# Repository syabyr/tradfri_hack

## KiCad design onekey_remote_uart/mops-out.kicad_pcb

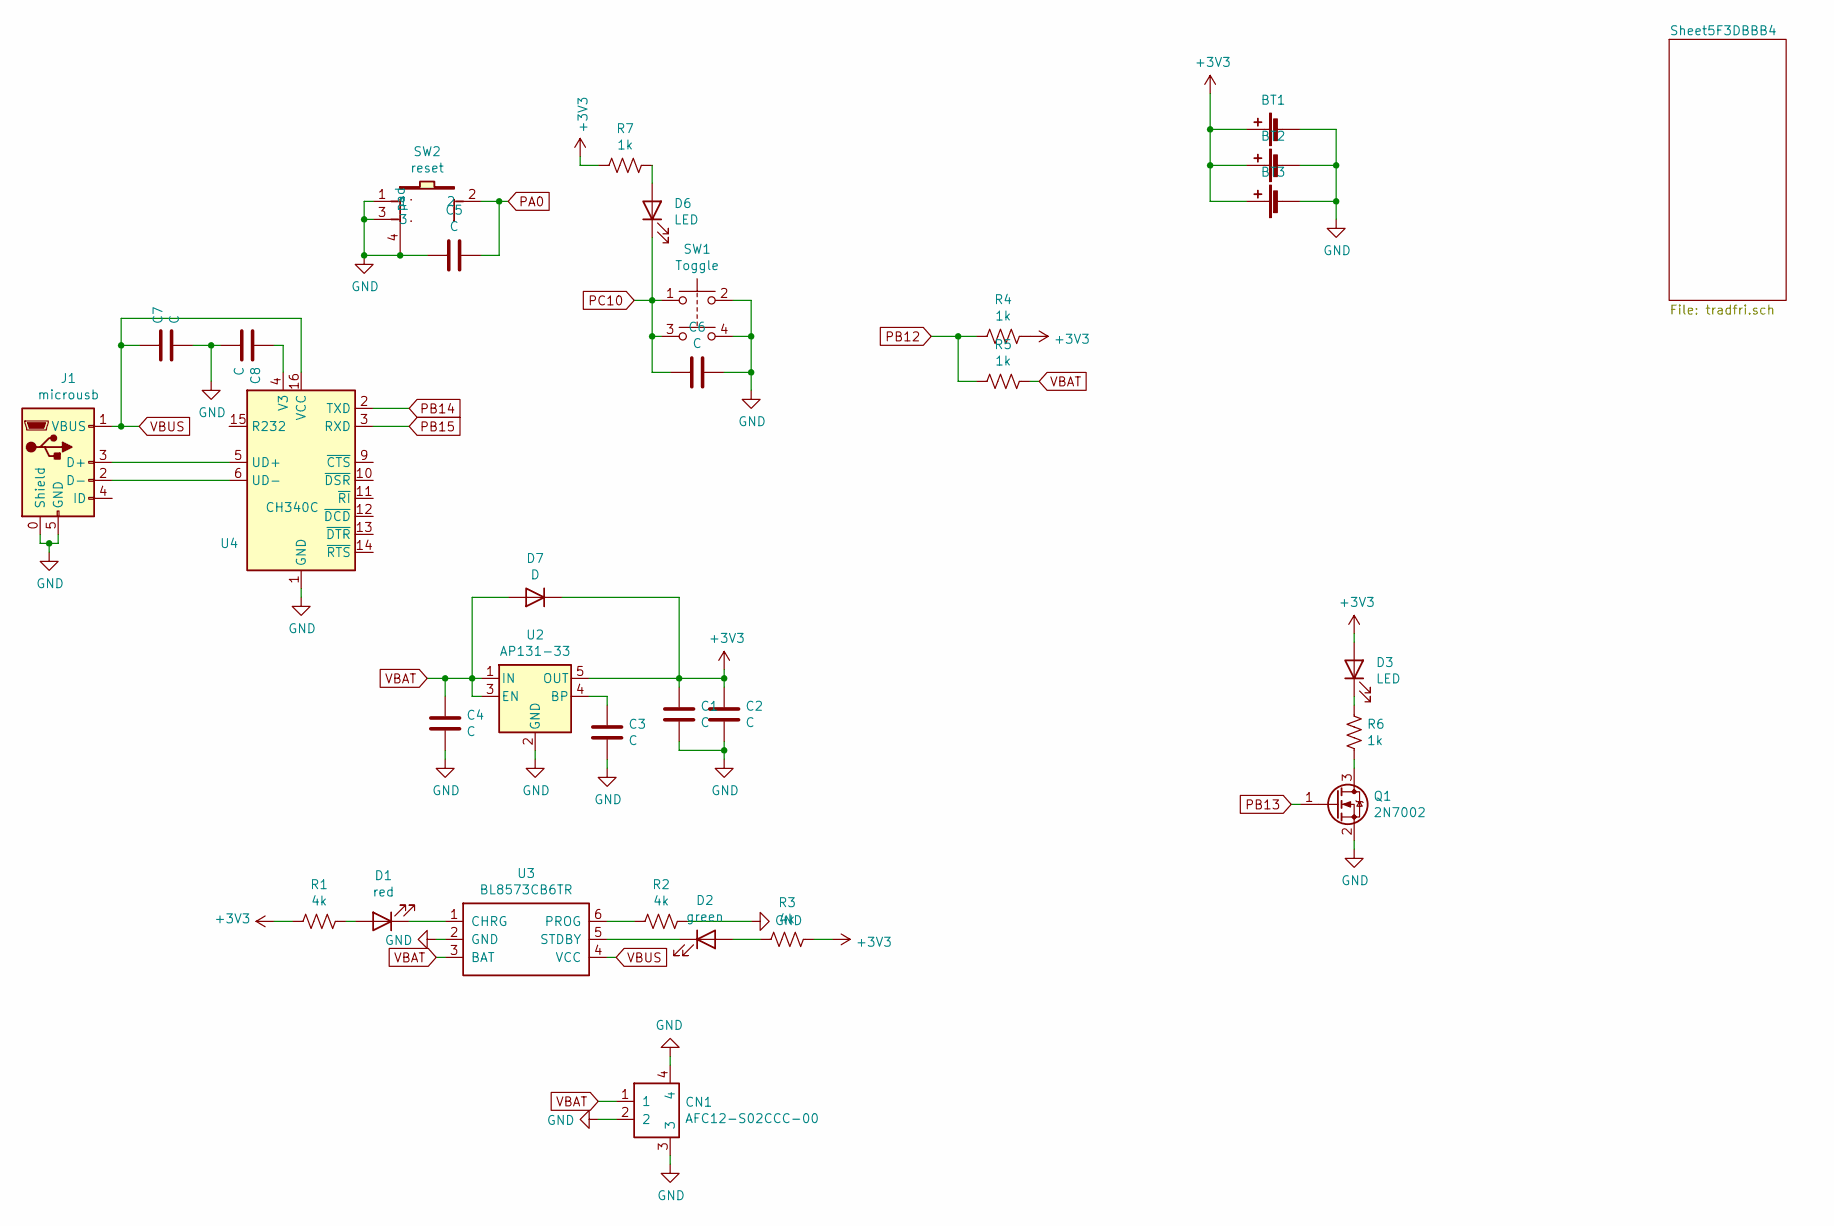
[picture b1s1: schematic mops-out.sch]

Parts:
BT1: Battery_Cell; CR2032_HOUSING
BT2: Battery_Cell; BAT-TH_BS-2-1
BT3: Battery_Cell; BAT-TH_CR2032-BS-6-1
C1, C3, C7, C8: C; C_0402_1005Metric_Pad0.74x0.62mm_HandSolder
C2, C4, C5, C6: C; C_0603_1608Metric_Pad1.08x0.95mm_HandSolder
CN1: AFC12-S02CCC-00; CONN-SMD_AFC12-S02CCC-00
D1: red; LED_0603_1608Metric_Pad1.05x0.95mm_HandSolder
D2: green; LED_0603_1608Metric_Pad1.05x0.95mm_HandSolder
D3, D6: LED; LED_0805_2012Metric_Pad1.15x1.40mm_HandSolder
D7: D; D_0603_1608Metric_Castellated
J1: microusb; USB_Micro-B_Wuerth_629105150521_CircularHoles
Q1: 2N7002; SOT-23
R1, R2, R3: 4k; R_0402_1005Metric_Pad0.72x0.64mm_HandSolder
R4, R5, R6, R7: 1k; R_0603_1608Metric_Pad0.98x0.95mm_HandSolder
SW1: Toggle; KEY-SMD_4P-L5.2-W5.2-P3.70-LS6.4-MOPS
SW2: reset; KEY_ALPS_SKRTLBE010
U2: AP131-33; SOT-23-5
U3: BL8573CB6TR; SOT-23-6_Handsoldering
U4: CH340C; SOIC-16_3.9x9.9mm_P1.27mm

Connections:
+3V3: BT1.1 (+), BT2.1 (+), BT3.1 (+), C1.1, C2.1, D3.2 (A), D7.1 (K), R1.2, R3.1, R4.1, R7.2, U2.5 (OUT); also elsewhere on the board
GND: BT1.2 (-), BT2.2 (-), BT3.2 (-), C1.2, C2.2, C3.2, C4.2, C5.2, C6.1, C7.2, C8.2, CN1.2, CN1.3, CN1.4, J1.0 (Shield), J1.5 (GND), Q1.2 (S), R2.1, SW1.2, SW1.4, SW2.1, SW2.3, SW2.4 (pad), U2.2 (GND), U3.2 (GND), U4.1 (GND); also elsewhere on the board
unnamed: C3.1, U2.4 (BP)
unnamed: C8.1, U4.4 (V3)
unnamed: D1.1 (K), U3.1 (CHRG)
unnamed: D1.2 (A), R1.1
unnamed: D2.1 (K), U3.5 (STDBY)
unnamed: D2.2 (A), R3.2
unnamed: D3.1 (K), R6.1
unnamed: D6.2 (A), R7.1
unnamed: J1.2 (D-), U4.6 (UD-)
unnamed: J1.3 (D+), U4.5 (UD+)
unnamed: Q1.3 (D), R6.2
unnamed: R2.2, U3.6 (PROG)
PA0: C5.1, SW2.2; also elsewhere on the board
PB12: R4.2, R5.2; also elsewhere on the board
PB13: Q1.1 (G); also elsewhere on the board
PB14: U4.2 (TXD); also elsewhere on the board
PB15: U4.3 (RXD); also elsewhere on the board
PC10: C6.2, D6.1 (K), SW1.1, SW1.3; also elsewhere on the board
VBAT: C4.1, CN1.1, D7.2 (A), R5.1, U2.1 (IN), U2.3 (EN), U3.3 (BAT)
VBUS: C7.1, J1.1 (VBUS), U3.4 (VCC), U4.16 (VCC)

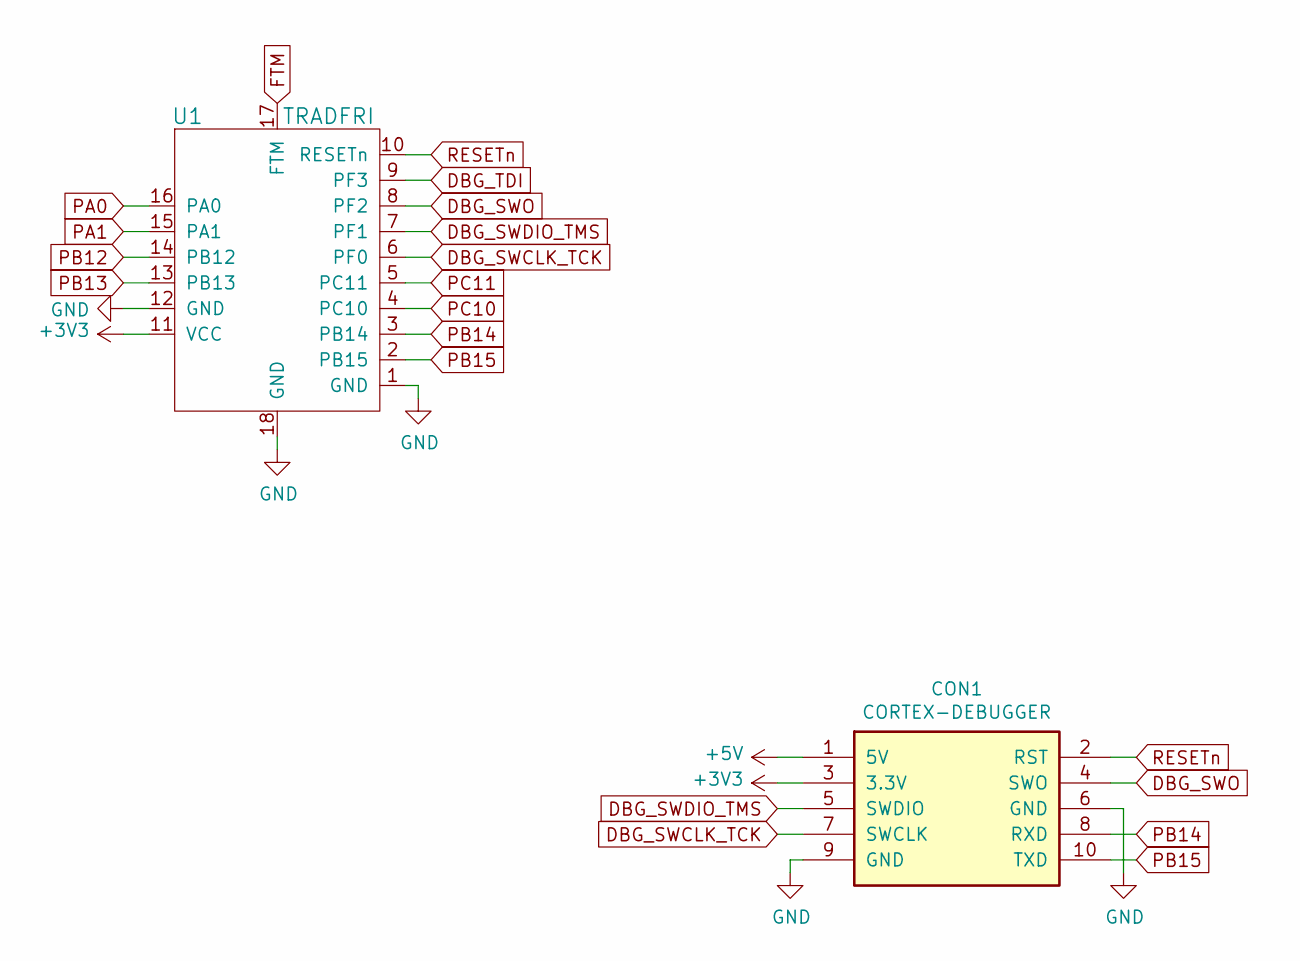
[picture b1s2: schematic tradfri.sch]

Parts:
CON1: CORTEX-DEBUGGER; debugger_2x05_P1.27mm_Vertical
U1: TRADFRI

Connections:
+3V3: CON1.3 (3.3V), U1.11 (VCC); also elsewhere on the board
+5V: CON1.1 (5V)
DBG_SWCLK_TCK: CON1.7 (SWCLK), U1.6 (PF0)
DBG_SWDIO_TMS: CON1.5 (SWDIO), U1.7 (PF1)
DBG_SWO: CON1.4 (SWO), U1.8 (PF2)
DBG_TDI: U1.9 (PF3)
FTM: U1.17 (FTM)
GND: CON1.6 (GND), CON1.9 (GND), U1.1 (GND), U1.12 (GND), U1.18 (GND); also elsewhere on the board
PA0: U1.16 (PA0); also elsewhere on the board
PA1: U1.15 (PA1)
PB12: U1.14 (PB12); also elsewhere on the board
PB13: U1.13 (PB13); also elsewhere on the board
PB14: CON1.8 (RXD), U1.3 (PB14); also elsewhere on the board
PB15: CON1.10 (TXD), U1.2 (PB15); also elsewhere on the board
PC10: U1.4 (PC10); also elsewhere on the board
PC11: U1.5 (PC11)
RESETn: CON1.2 (RST), U1.10 (RESETn)

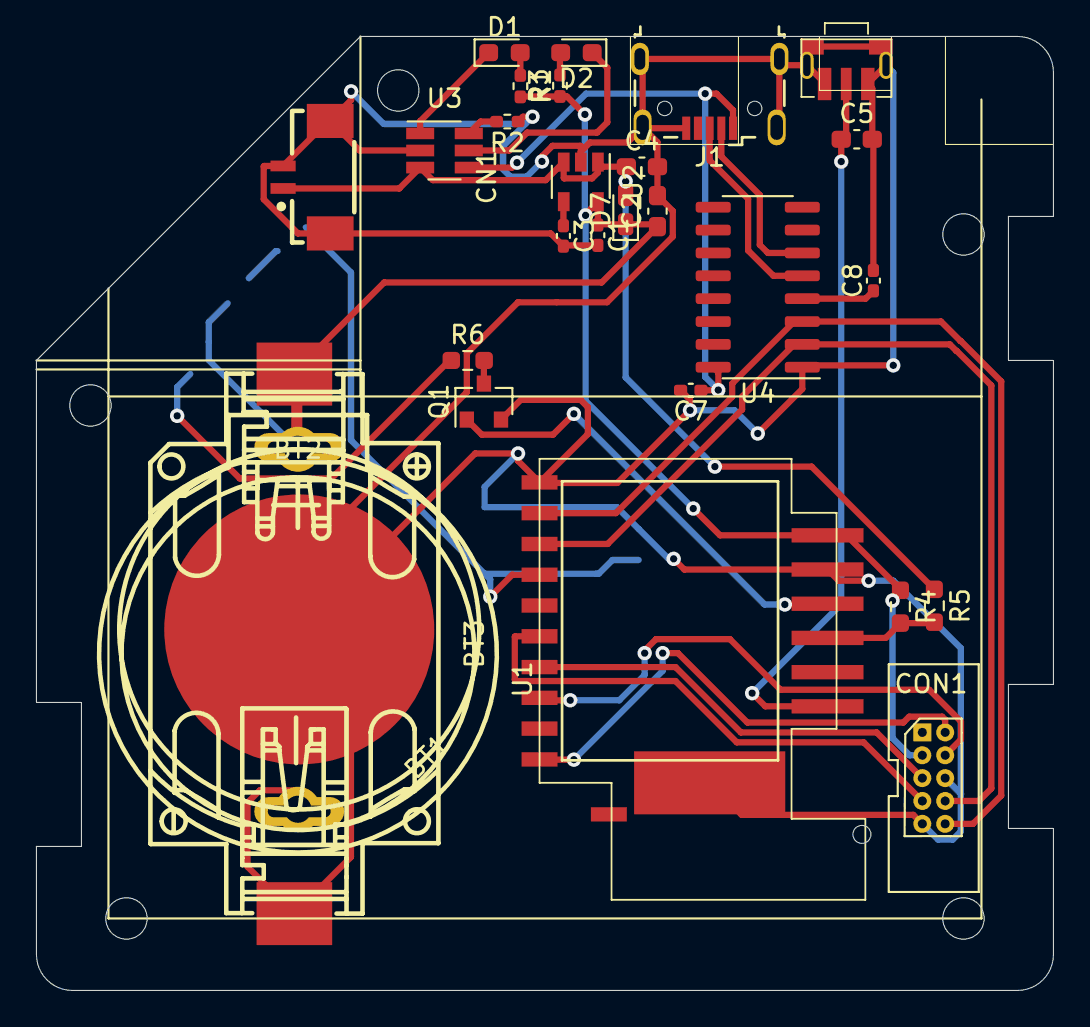
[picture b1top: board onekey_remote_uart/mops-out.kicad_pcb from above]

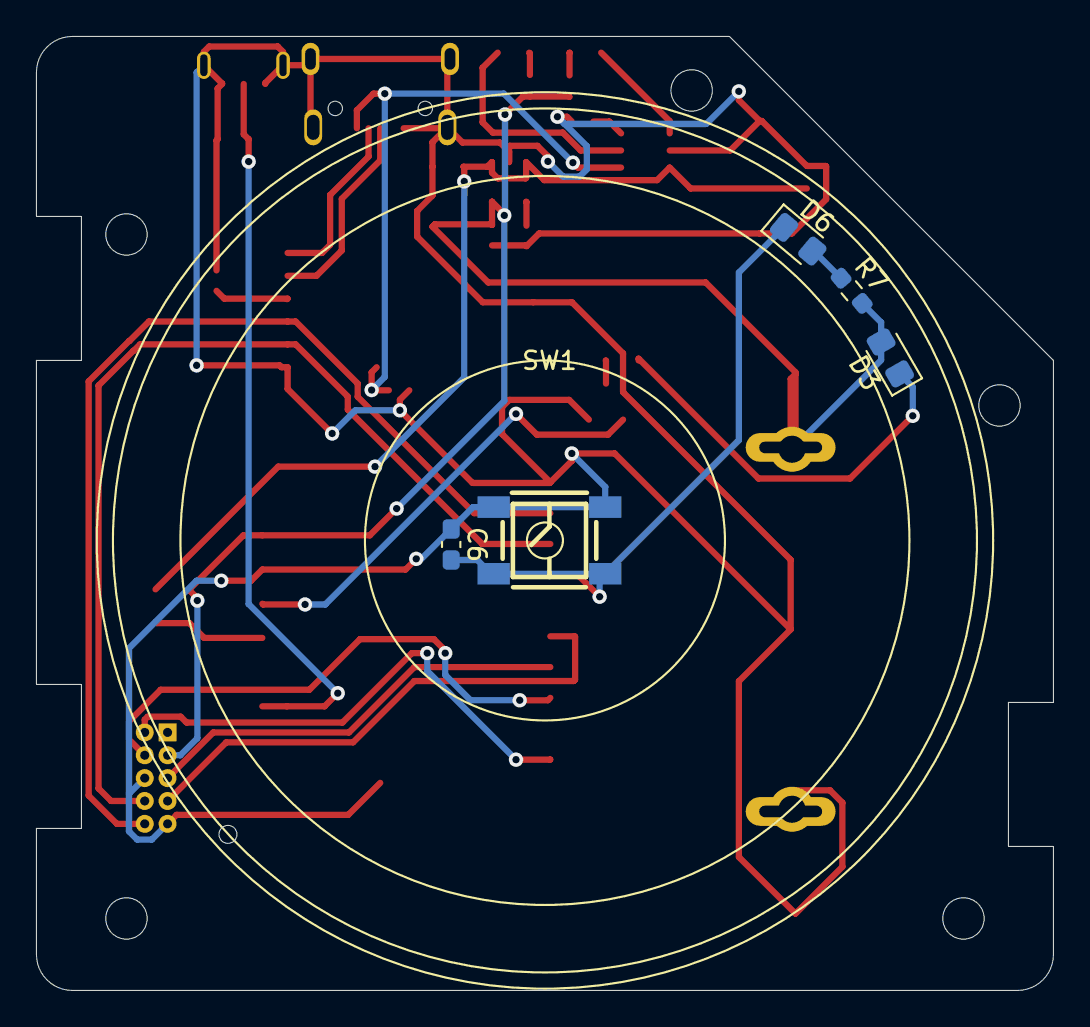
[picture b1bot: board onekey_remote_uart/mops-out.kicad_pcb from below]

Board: 2 copper layers, 56.5 x 53.0 mm, 33 parts (5 on the bottom side), 26 nets.

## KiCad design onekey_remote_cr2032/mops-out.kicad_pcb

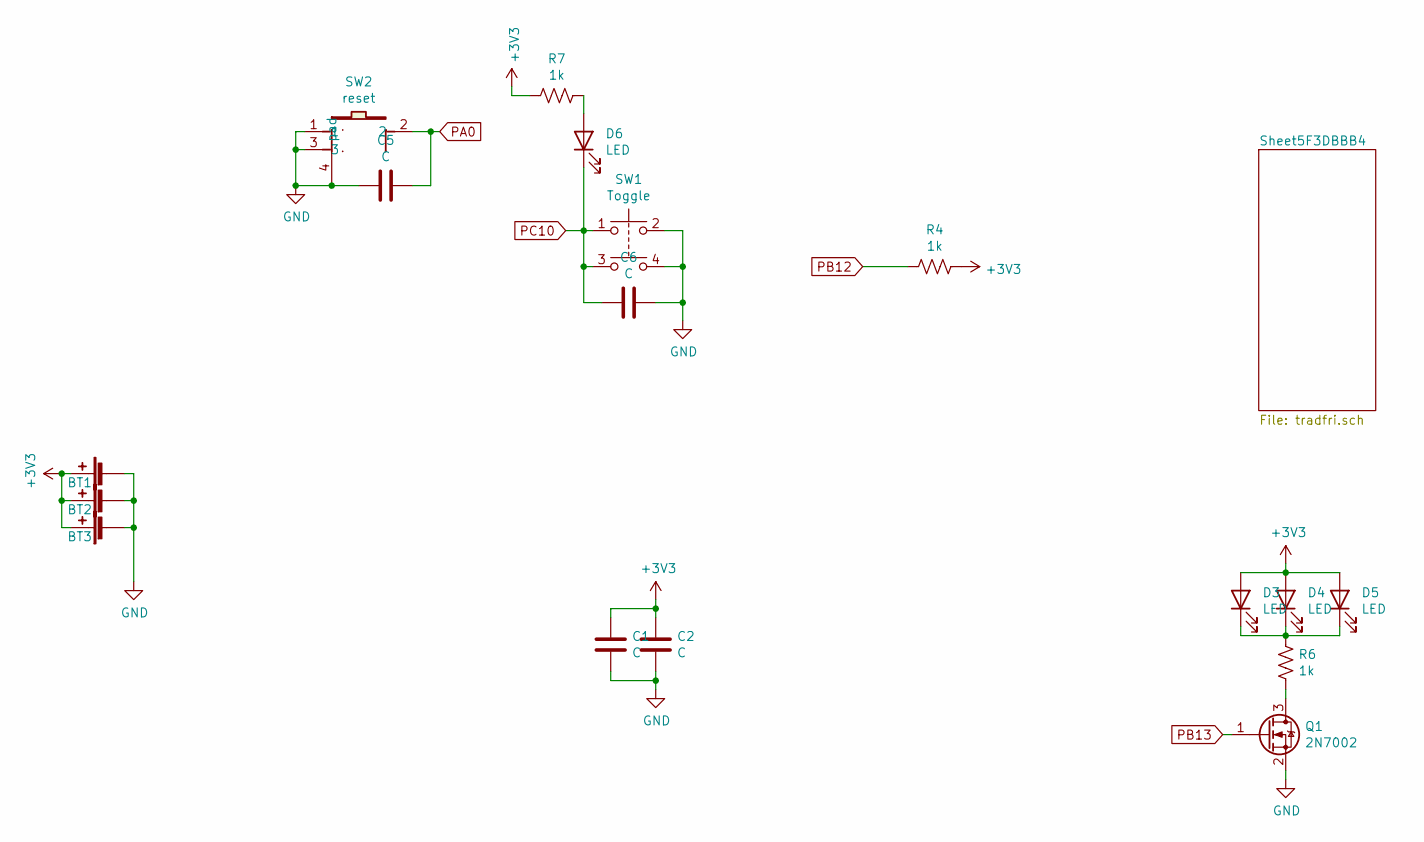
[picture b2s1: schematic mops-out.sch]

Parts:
BT1: Battery_Cell; CR2032_HOUSING
BT2: Battery_Cell; BAT-TH_BS-2-1
BT3: Battery_Cell; BAT-TH_CR2032-BS-6-1
C1: C; C_0402_1005Metric_Pad0.74x0.62mm_HandSolder
C2, C5, C6: C; C_0603_1608Metric_Pad1.08x0.95mm_HandSolder
D3, D4, D5, D6: LED; LED_0805_2012Metric_Pad1.15x1.40mm_HandSolder
Q1: 2N7002; SOT-23
R4, R6, R7: 1k; R_0603_1608Metric_Pad0.98x0.95mm_HandSolder
SW1: Toggle; KEY-SMD_4P-L5.2-W5.2-P3.70-LS6.4-MOPS
SW2: reset; KEY_ALPS_SKRTLBE010

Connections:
+3V3: BT1.1 (+), BT2.1 (+), BT3.1 (+), C1.1, C2.1, D3.2 (A), D4.2 (A), D5.2 (A), R4.1, R7.2; also elsewhere on the board
GND: BT1.2 (-), BT2.2 (-), BT3.2 (-), C1.2, C2.2, C5.2, C6.1, Q1.2 (S), SW1.2, SW1.4, SW2.1, SW2.3, SW2.4 (pad); also elsewhere on the board
unnamed: D3.1 (K), D4.1 (K), D5.1 (K), R6.1
unnamed: D6.2 (A), R7.1
unnamed: Q1.3 (D), R6.2
PA0: C5.1, SW2.2; also elsewhere on the board
PB12: R4.2; also elsewhere on the board
PB13: Q1.1 (G); also elsewhere on the board
PC10: C6.2, D6.1 (K), SW1.1, SW1.3; also elsewhere on the board

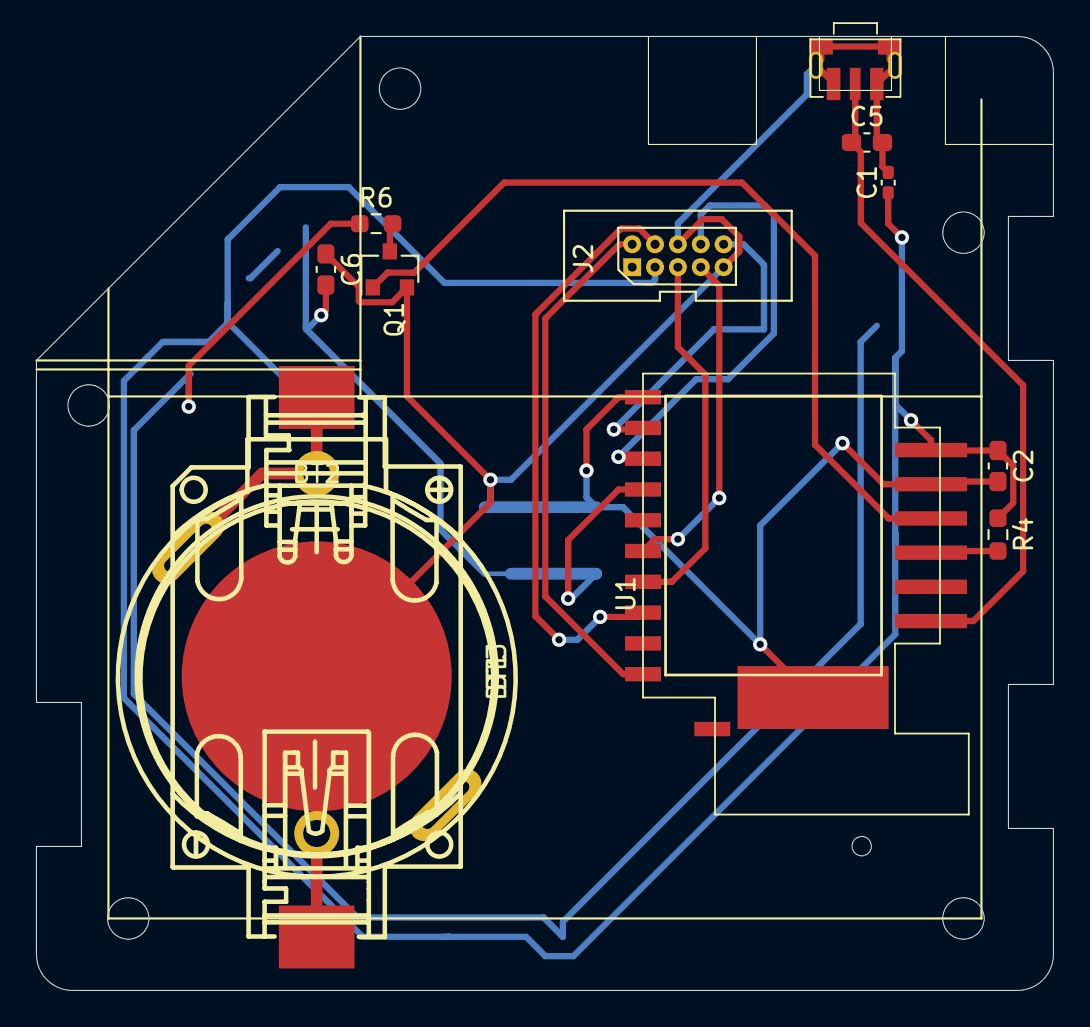
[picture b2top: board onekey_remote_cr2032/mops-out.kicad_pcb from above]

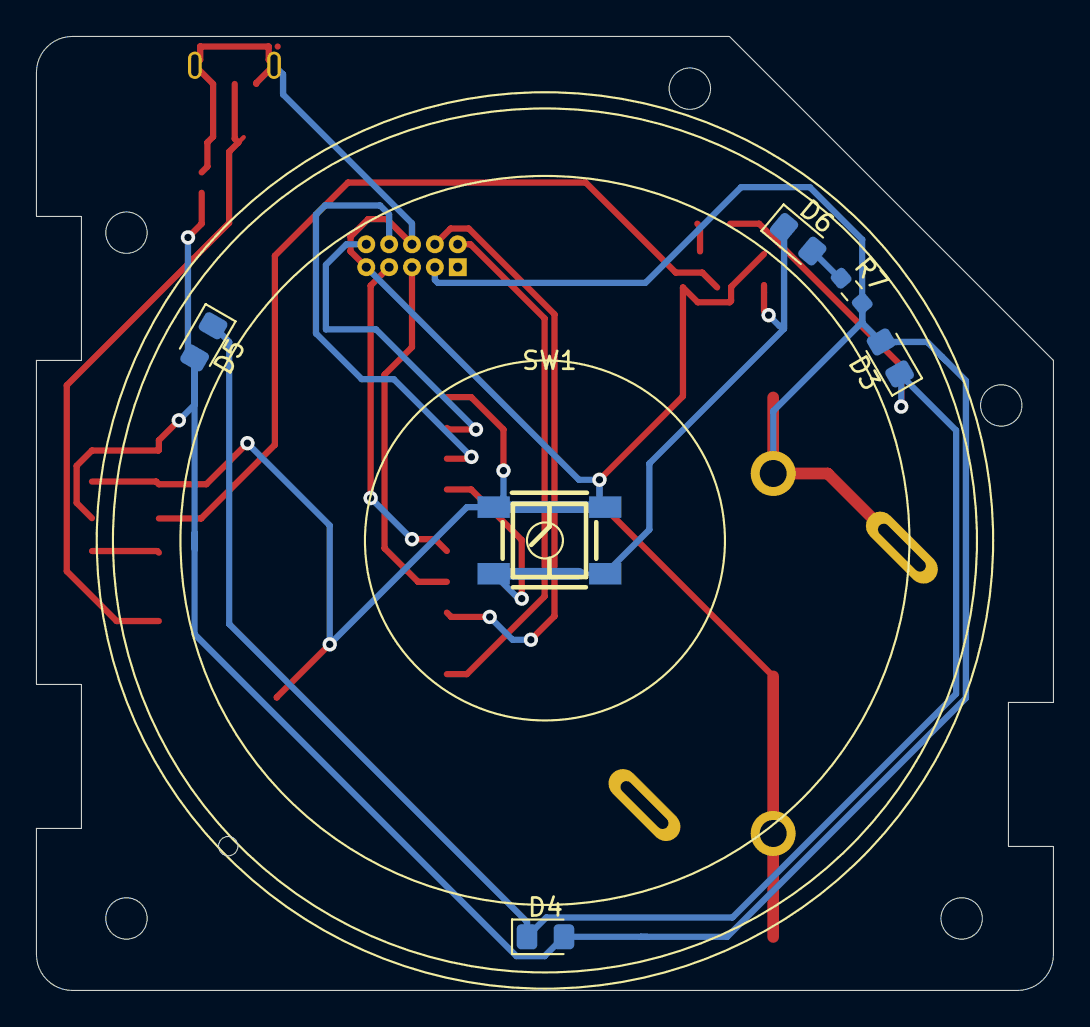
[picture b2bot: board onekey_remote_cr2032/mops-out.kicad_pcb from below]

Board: 2 copper layers, 56.5 x 53.0 mm, 19 parts (6 on the bottom side), 15 nets.

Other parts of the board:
J2: tradfri_debugger; debugger_2x05_P1.27mm_Vertical
U1: TRADFRI

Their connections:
+3V3: J2.3, U1.11; also elsewhere on the board
DBG_SWCLK_TCK: J2.7, U1.6
DBG_SWDIO_TMS: J2.5, U1.7
DBG_SWO: J2.4, U1.8
GND: J2.6, J2.9, U1.1, U1.12, U1.18; also elsewhere on the board
PA0: U1.16; also elsewhere on the board
PB12: U1.14; also elsewhere on the board
PB13: U1.13; also elsewhere on the board
PB14: J2.8, U1.3
PB15: J2.10, U1.2
PC10: U1.4; also elsewhere on the board
RESETn: J2.2, U1.10

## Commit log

2021-02-02 onkey remote
2021-02-08 readme
2021-03-14 cr2032
2021-03-28 dsstore
2021-07-10 uart
